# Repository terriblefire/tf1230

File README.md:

# tf1230

TF1230 source files. 

Released in Creative Commons CC-BY-ND license. 

This is a NO DERIVATIVES LICENSE. You cannot modify it and distribute the modified version.

TF1230 is distributed with absolutely no warranty. If you make a mistake you could blow up your A1200. I take no responsibility for this. 

The TF1230 is an 030 accelerator fixed at 50Mhz with 64Mb of SDRAM (128Mb possible), and is intended to work with CF cards or IDE2SD card type devices. The IDE interface does not work with long cables. It is intended to be CHEAP Because thats pretty much all Amiga users care about. You need the ehide.device to use the onboard ide.

There was a design decision to make with the TF ide. Do we make it work as the default ide device and break PCMCIA support, do we add a rom on the card (and more expense) or do we just provide a driver that you can put in a cheap rom and run that way (or just run from disk). I figured the cheapest and least invasive option was the best for a home build solution.

**Before you start building :- You can buy these from Supaduper & AlenPPC (AmiBay) completely built for less than it will cost you to buy the parts and the time it will take you if you bill your time at minimum wage.**

Also do not ask me to reroute the board to a different DRC so you can use your local boardhouse. I dont feel like spending 100 hours of my time to save you $10. The DRC on this board is 7-7-7 and any boardhouse that doesnt totally suck can do this. Also it 4 layer and dont ask if i can be made 2 layer. The answer is no. 

If you need help with this the best place to get it is the exxos forum https://www.exxoshost.co.uk/forum/ 

The SDRAM Controller is derived from my Archie core and the clock controller code is designed to simulate a PLL with adjustable phase. 

This is not an exercise in German over engineering. Its engineered to do an exact task and nothing more. You will need to do the timing fixes or put a clock buffer on the clock line on this board. I didnt do this because i believe that the timing changes are needed on Amigas and not doing them is bad for them long term. Cards that let you get away without doing it are doing you a diservice. It would be like cards letting you go longer without a recap. Its 

That said you are free to sell this on your webshop provided you give credit and do not vastly overprice it. However CE marking is your own issue not mine. AmigaKit may not sell this ever... anyone else can. 

On the other hand if you have an actual firmware bugfix send me a pull request with testing evidence. It will be appreciated greatly. 

For crashes please check that the crash doesnt happen in WinUAE for a A1200 with A1200 IDE and 64MB ZIII Ram before making a bug report. Most of the crashes we have seen over the years are repeatable in that environment.

The purpose of this card is for you to get more enjoyment from your Amiga for very little money. Please do that.

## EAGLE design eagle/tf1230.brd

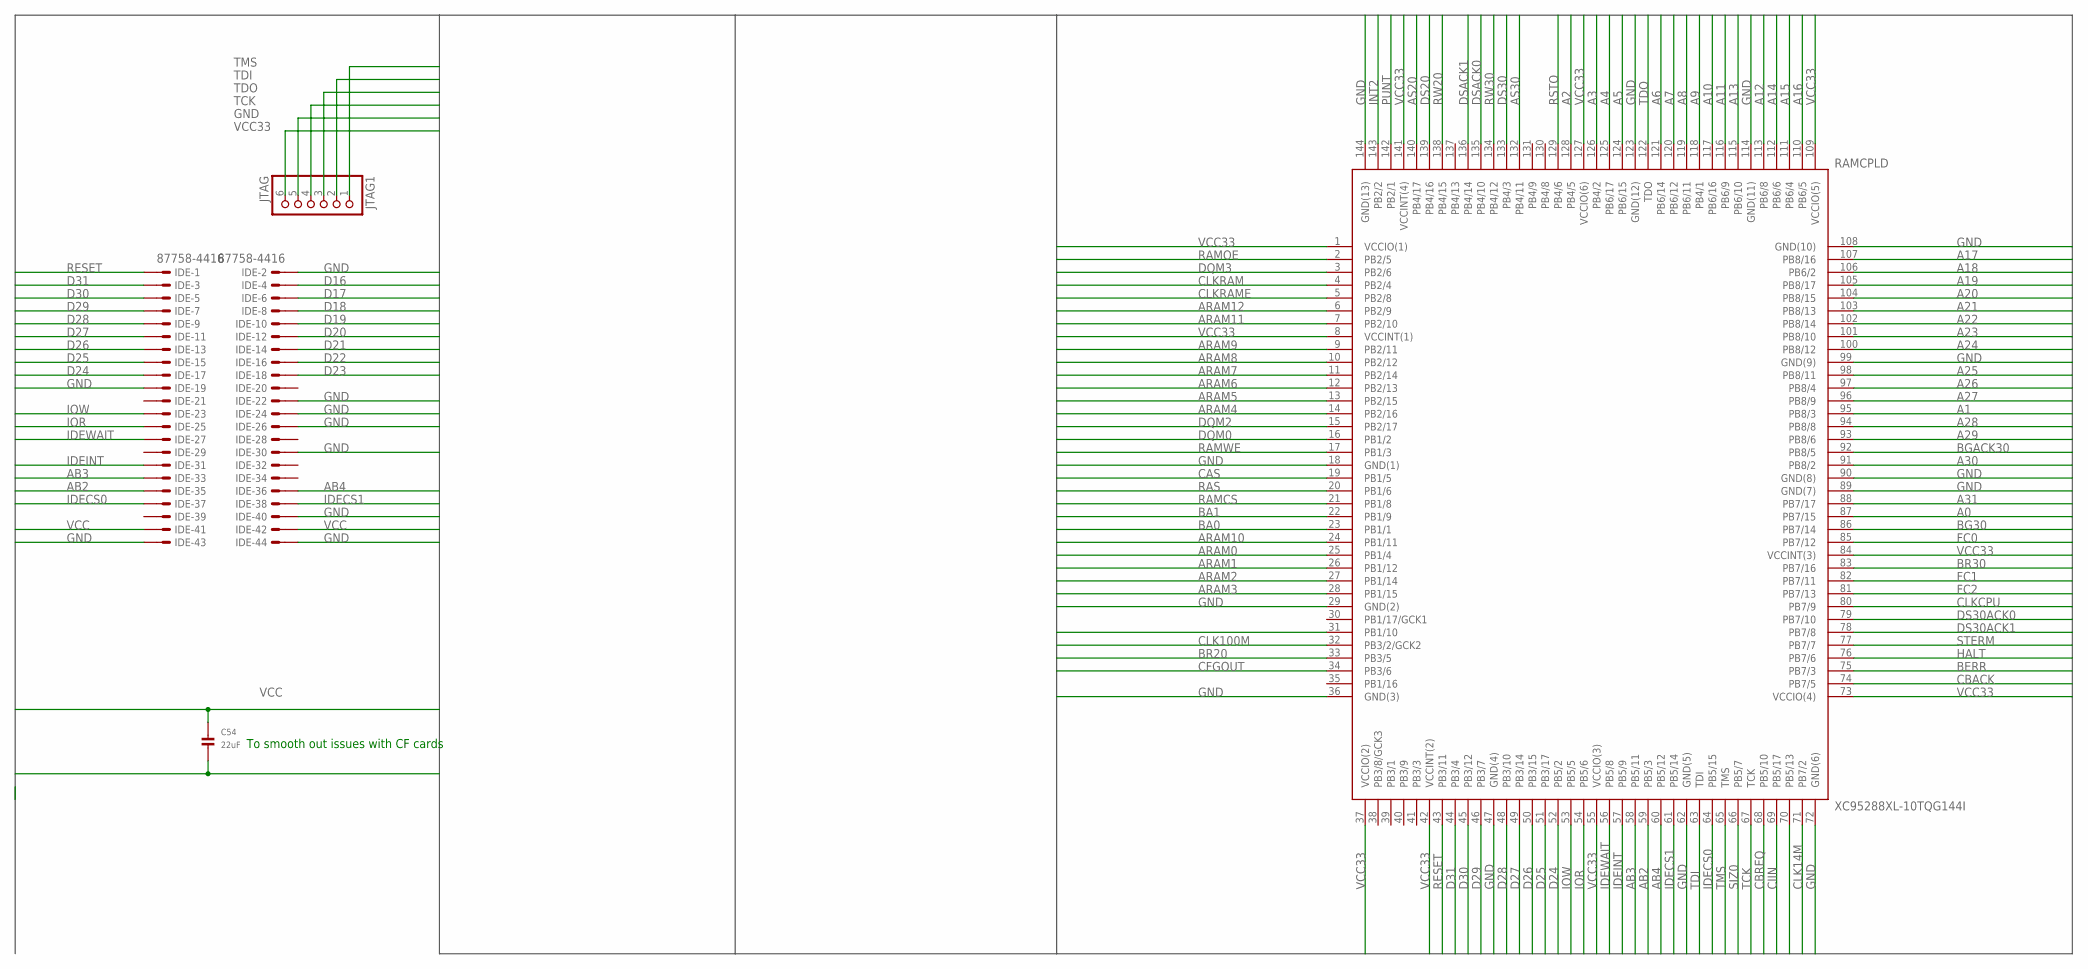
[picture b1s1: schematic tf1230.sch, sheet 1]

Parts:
C54: 22uF; 1206
IDE: 87758-4416
JTAG1: JTAG; 1X06_ROUND
RAMCPLD: XC95288XL-10TQG144I; SAMACSYS_PARTS_QFP50P2200X2200X160-144N

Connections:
A0: RAMCPLD.87 (PB7/15); also elsewhere on the board
A1: RAMCPLD.95 (PB8/3); also elsewhere on the board
A2: RAMCPLD.128 (PB4/5); also elsewhere on the board
A3: RAMCPLD.126 (PB4/2); also elsewhere on the board
A4: RAMCPLD.125 (PB6/17); also elsewhere on the board
A5: RAMCPLD.124 (PB6/15); also elsewhere on the board
A6: RAMCPLD.121 (PB6/14); also elsewhere on the board
A7: RAMCPLD.120 (PB6/12); also elsewhere on the board
A8: RAMCPLD.119 (PB6/11); also elsewhere on the board
A9: RAMCPLD.118 (PB4/1); also elsewhere on the board
A10: RAMCPLD.117 (PB6/16); also elsewhere on the board
A11: RAMCPLD.116 (PB6/9); also elsewhere on the board
A12: RAMCPLD.113 (PB6/8); also elsewhere on the board
A13: RAMCPLD.115 (PB6/10); also elsewhere on the board
A14: RAMCPLD.112 (PB6/6); also elsewhere on the board
A15: RAMCPLD.111 (PB6/4); also elsewhere on the board
A16: RAMCPLD.110 (PB6/5); also elsewhere on the board
A17: RAMCPLD.107 (PB8/16); also elsewhere on the board
A18: RAMCPLD.106 (PB6/2); also elsewhere on the board
A19: RAMCPLD.105 (PB8/17); also elsewhere on the board
A20: RAMCPLD.104 (PB8/15); also elsewhere on the board
A21: RAMCPLD.103 (PB8/13); also elsewhere on the board
A22: RAMCPLD.102 (PB8/14); also elsewhere on the board
A23: RAMCPLD.101 (PB8/10); also elsewhere on the board
A24: RAMCPLD.100 (PB8/12); also elsewhere on the board
A25: RAMCPLD.98 (PB8/11); also elsewhere on the board
A26: RAMCPLD.97 (PB8/4); also elsewhere on the board
A27: RAMCPLD.96 (PB8/9); also elsewhere on the board
A28: RAMCPLD.94 (PB8/8); also elsewhere on the board
A29: RAMCPLD.93 (PB8/6); also elsewhere on the board
A30: RAMCPLD.91 (PB8/2); also elsewhere on the board
A31: RAMCPLD.88 (PB7/17); also elsewhere on the board
AB2: IDE.35, RAMCPLD.59 (PB5/3)
AB3: IDE.33, RAMCPLD.58 (PB5/11)
AB4: IDE.36, RAMCPLD.60 (PB5/12)
ARAM0: RAMCPLD.25 (PB1/4); also elsewhere on the board
ARAM1: RAMCPLD.26 (PB1/12); also elsewhere on the board
ARAM2: RAMCPLD.27 (PB1/14); also elsewhere on the board
ARAM3: RAMCPLD.28 (PB1/15); also elsewhere on the board
ARAM4: RAMCPLD.14 (PB2/16); also elsewhere on the board
ARAM5: RAMCPLD.13 (PB2/15); also elsewhere on the board
ARAM6: RAMCPLD.12 (PB2/13); also elsewhere on the board
ARAM7: RAMCPLD.11 (PB2/14); also elsewhere on the board
ARAM8: RAMCPLD.10 (PB2/12); also elsewhere on the board
ARAM9: RAMCPLD.9 (PB2/11); also elsewhere on the board
ARAM10: RAMCPLD.24 (PB1/11); also elsewhere on the board
ARAM11: RAMCPLD.7 (PB2/10); also elsewhere on the board
ARAM12: RAMCPLD.6 (PB2/9); also elsewhere on the board
AS20: RAMCPLD.140 (PB4/17); also elsewhere on the board
AS30: RAMCPLD.132 (PB4/11); also elsewhere on the board
BA0: RAMCPLD.23 (PB1/1); also elsewhere on the board
BA1: RAMCPLD.22 (PB1/9); also elsewhere on the board
BERR: RAMCPLD.75 (PB7/3); also elsewhere on the board
BG30: RAMCPLD.86 (PB7/14); also elsewhere on the board
BGACK30: RAMCPLD.92 (PB8/5); also elsewhere on the board
BR20: RAMCPLD.33 (PB3/5); also elsewhere on the board
BR30: RAMCPLD.83 (PB7/16); also elsewhere on the board
CAS: RAMCPLD.19 (PB1/5); also elsewhere on the board
CBACK: RAMCPLD.74 (PB7/5); also elsewhere on the board
CBREQ: RAMCPLD.68 (PB5/10); also elsewhere on the board
CFGOUT: RAMCPLD.34 (PB3/6); also elsewhere on the board
CIIN: RAMCPLD.69 (PB5/17); also elsewhere on the board
CLK14M: RAMCPLD.71 (PB7/2); also elsewhere on the board
CLK100M: RAMCPLD.32 (PB3/2/GCK2); also elsewhere on the board
CLKCPU: RAMCPLD.80 (PB7/9); also elsewhere on the board
CLKRAM: RAMCPLD.4 (PB2/4); also elsewhere on the board
CLKRAME: RAMCPLD.5 (PB2/8); also elsewhere on the board
D16: IDE.4; also elsewhere on the board
D17: IDE.6; also elsewhere on the board
D18: IDE.8; also elsewhere on the board
D19: IDE.10; also elsewhere on the board
D20: IDE.12; also elsewhere on the board
D21: IDE.14; also elsewhere on the board
D22: IDE.16; also elsewhere on the board
D23: IDE.18; also elsewhere on the board
D24: IDE.17, RAMCPLD.52 (PB5/2); also elsewhere on the board
D25: IDE.15, RAMCPLD.51 (PB3/17); also elsewhere on the board
D26: IDE.13, RAMCPLD.50 (PB3/15); also elsewhere on the board
D27: IDE.11, RAMCPLD.49 (PB3/14); also elsewhere on the board
D28: IDE.9, RAMCPLD.48 (PB3/10); also elsewhere on the board
D29: IDE.7, RAMCPLD.46 (PB3/7); also elsewhere on the board
D30: IDE.5, RAMCPLD.45 (PB3/12); also elsewhere on the board
D31: IDE.3, RAMCPLD.44 (PB3/4); also elsewhere on the board
DQM0: RAMCPLD.16 (PB1/2); also elsewhere on the board
DQM1: RAMCPLD.31 (PB1/10); also elsewhere on the board
DQM2: RAMCPLD.15 (PB2/17); also elsewhere on the board
DQM3: RAMCPLD.3 (PB2/6); also elsewhere on the board
DS20: RAMCPLD.139 (PB4/16); also elsewhere on the board
DS30: RAMCPLD.133 (PB4/3); also elsewhere on the board
DS30ACK0: RAMCPLD.79 (PB7/10); also elsewhere on the board
DS30ACK1: RAMCPLD.78 (PB7/8); also elsewhere on the board
DSACK0: RAMCPLD.135 (PB4/10); also elsewhere on the board
DSACK1: RAMCPLD.136 (PB4/14); also elsewhere on the board
FC0: RAMCPLD.85 (PB7/12); also elsewhere on the board
FC1: RAMCPLD.82 (PB7/11); also elsewhere on the board
FC2: RAMCPLD.81 (PB7/13); also elsewhere on the board
GND: C54.2, IDE.2, IDE.19, IDE.22, IDE.24, IDE.26, IDE.30, IDE.40, IDE.43, IDE.44, JTAG1.5, RAMCPLD.18 (GND(1)), RAMCPLD.29 (GND(2)), RAMCPLD.36 (GND(3)), RAMCPLD.47 (GND(4)), RAMCPLD.62 (GND(5)), RAMCPLD.72 (GND(6)), RAMCPLD.89 (GND(7)), RAMCPLD.90 (GND(8)), RAMCPLD.99 (GND(9)), RAMCPLD.108 (GND(10)), RAMCPLD.114 (GND(11)), RAMCPLD.123 (GND(12)), RAMCPLD.144 (GND(13)); also elsewhere on the board
HALT: RAMCPLD.76 (PB7/6); also elsewhere on the board
IDECS0: IDE.37, RAMCPLD.64 (PB5/15)
IDECS1: IDE.38, RAMCPLD.61 (PB5/14)
IDEINT: IDE.31, RAMCPLD.57 (PB5/9); also elsewhere on the board
IDEWAIT: IDE.27, RAMCPLD.56 (PB5/8); also elsewhere on the board
INT2: RAMCPLD.143 (PB2/2); also elsewhere on the board
IOR: IDE.25, RAMCPLD.54 (PB5/6)
IOW: IDE.23, RAMCPLD.53 (PB5/5)
PUNT: RAMCPLD.142 (PB2/1); also elsewhere on the board
RAMCS: RAMCPLD.21 (PB1/8); also elsewhere on the board
RAMOE: RAMCPLD.2 (PB2/5); also elsewhere on the board
RAMWE: RAMCPLD.17 (PB1/3); also elsewhere on the board
RAS: RAMCPLD.20 (PB1/6); also elsewhere on the board
RESET: IDE.1, RAMCPLD.43 (PB3/11); also elsewhere on the board
RSTO: RAMCPLD.129 (PB4/6); also elsewhere on the board
RW20: RAMCPLD.138 (PB4/15); also elsewhere on the board
RW30: RAMCPLD.134 (PB4/12); also elsewhere on the board
SIZ0: RAMCPLD.66 (PB5/7); also elsewhere on the board
SIZ1: RAMCPLD.70 (PB5/13); also elsewhere on the board
STERM: RAMCPLD.77 (PB7/7); also elsewhere on the board
TCK: JTAG1.4, RAMCPLD.67 (TCK)
TDI: JTAG1.2, RAMCPLD.63 (TDI)
TDO: JTAG1.3, RAMCPLD.122 (TDO)
TMS: JTAG1.1, RAMCPLD.65 (TMS)
VCC: C54.1, IDE.41, IDE.42; also elsewhere on the board
VCC33: JTAG1.6, RAMCPLD.1 (VCCIO(1)), RAMCPLD.8 (VCCINT(1)), RAMCPLD.37 (VCCIO(2)), RAMCPLD.42 (VCCINT(2)), RAMCPLD.55 (VCCIO(3)), RAMCPLD.73 (VCCIO(4)), RAMCPLD.84 (VCCINT(3)), RAMCPLD.109 (VCCIO(5)), RAMCPLD.127 (VCCIO(6)), RAMCPLD.141 (VCCINT(4)); also elsewhere on the board

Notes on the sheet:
To smooth out issues with CF cards

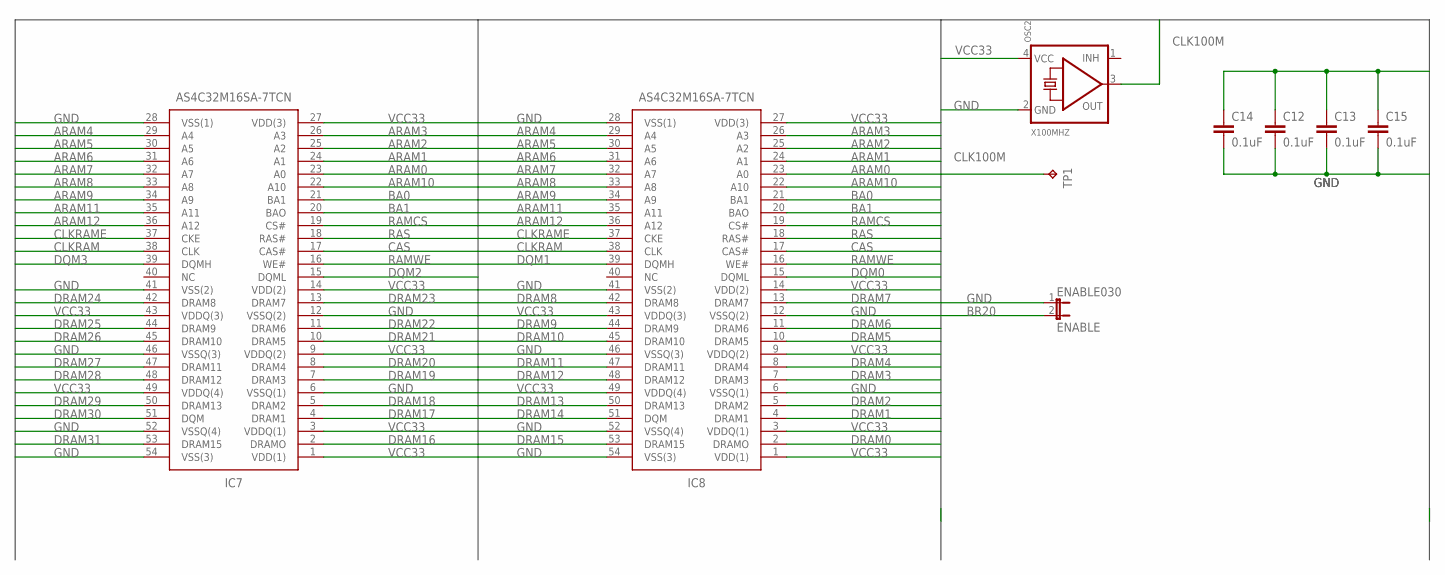
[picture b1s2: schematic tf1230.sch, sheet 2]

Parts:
C12, C13, C14, C15: 0.1uF; 0603-CAP
ENABLE030: ENABLE; 1X02
IC7, IC8: AS4C32M16SA-7TCN; SOP80P1176X120-54N
OSC2: X100MHZ; OSC_7X5MM
TP1: TPB1,27; B1,27

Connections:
ARAM0: IC7.23 (A0), IC8.23 (A0); also elsewhere on the board
ARAM1: IC7.24 (A1), IC8.24 (A1); also elsewhere on the board
ARAM2: IC7.25 (A2), IC8.25 (A2); also elsewhere on the board
ARAM3: IC7.26 (A3), IC8.26 (A3); also elsewhere on the board
ARAM4: IC7.29 (A4), IC8.29 (A4); also elsewhere on the board
ARAM5: IC7.30 (A5), IC8.30 (A5); also elsewhere on the board
ARAM6: IC7.31 (A6), IC8.31 (A6); also elsewhere on the board
ARAM7: IC7.32 (A7), IC8.32 (A7); also elsewhere on the board
ARAM8: IC7.33 (A8), IC8.33 (A8); also elsewhere on the board
ARAM9: IC7.34 (A9), IC8.34 (A9); also elsewhere on the board
ARAM10: IC7.22 (A10), IC8.22 (A10); also elsewhere on the board
ARAM11: IC7.35 (A11), IC8.35 (A11); also elsewhere on the board
ARAM12: IC7.36 (A12), IC8.36 (A12); also elsewhere on the board
BA0: IC7.21 (BA1), IC8.21 (BA1); also elsewhere on the board
BA1: IC7.20 (BAO), IC8.20 (BAO); also elsewhere on the board
BR20: ENABLE030.2; also elsewhere on the board
CAS: IC7.17 (CAS#), IC8.17 (CAS#); also elsewhere on the board
CLK100M: OSC2.3 (OUT), TP1.TP; also elsewhere on the board
CLKRAM: IC7.38 (CLK), IC8.38 (CLK); also elsewhere on the board
CLKRAME: IC7.37 (CKE), IC8.37 (CKE); also elsewhere on the board
DQM0: IC8.15 (DQML); also elsewhere on the board
DQM1: IC8.39 (DQMH); also elsewhere on the board
DQM2: IC7.15 (DQML); also elsewhere on the board
DQM3: IC7.39 (DQMH); also elsewhere on the board
DRAM0: IC8.2 (DRAMO); also elsewhere on the board
DRAM1: IC8.4 (DRAM1); also elsewhere on the board
DRAM2: IC8.5 (DRAM2); also elsewhere on the board
DRAM3: IC8.7 (DRAM3); also elsewhere on the board
DRAM4: IC8.8 (DRAM4); also elsewhere on the board
DRAM5: IC8.10 (DRAM5); also elsewhere on the board
DRAM6: IC8.11 (DRAM6); also elsewhere on the board
DRAM7: IC8.13 (DRAM7); also elsewhere on the board
DRAM8: IC8.42 (DRAM8); also elsewhere on the board
DRAM9: IC8.44 (DRAM9); also elsewhere on the board
DRAM10: IC8.45 (DRAM10); also elsewhere on the board
DRAM11: IC8.47 (DRAM11); also elsewhere on the board
DRAM12: IC8.48 (DRAM12); also elsewhere on the board
DRAM13: IC8.50 (DRAM13); also elsewhere on the board
DRAM14: IC8.51 (DQM); also elsewhere on the board
DRAM15: IC8.53 (DRAM15); also elsewhere on the board
DRAM16: IC7.2 (DRAMO); also elsewhere on the board
DRAM17: IC7.4 (DRAM1); also elsewhere on the board
DRAM18: IC7.5 (DRAM2); also elsewhere on the board
DRAM19: IC7.7 (DRAM3); also elsewhere on the board
DRAM20: IC7.8 (DRAM4); also elsewhere on the board
DRAM21: IC7.10 (DRAM5); also elsewhere on the board
DRAM22: IC7.11 (DRAM6); also elsewhere on the board
DRAM23: IC7.13 (DRAM7); also elsewhere on the board
DRAM24: IC7.42 (DRAM8); also elsewhere on the board
DRAM25: IC7.44 (DRAM9); also elsewhere on the board
DRAM26: IC7.45 (DRAM10); also elsewhere on the board
DRAM27: IC7.47 (DRAM11); also elsewhere on the board
DRAM28: IC7.48 (DRAM12); also elsewhere on the board
DRAM29: IC7.50 (DRAM13); also elsewhere on the board
DRAM30: IC7.51 (DQM); also elsewhere on the board
DRAM31: IC7.53 (DRAM15); also elsewhere on the board
GND: C12.2, C13.2, C14.2, C15.2, ENABLE030.1, IC7.6 (VSSQ(1)), IC7.12 (VSSQ(2)), IC7.28 (VSS(1)), IC7.41 (VSS(2)), IC7.46 (VSSQ(3)), IC7.52 (VSSQ(4)), IC7.54 (VSS(3)), IC8.6 (VSSQ(1)), IC8.12 (VSSQ(2)), IC8.28 (VSS(1)), IC8.41 (VSS(2)), IC8.46 (VSSQ(3)), IC8.52 (VSSQ(4)), IC8.54 (VSS(3)), OSC2.2 (GND); also elsewhere on the board
RAMCS: IC7.19 (CS#), IC8.19 (CS#); also elsewhere on the board
RAMWE: IC7.16 (WE#), IC8.16 (WE#); also elsewhere on the board
RAS: IC7.18 (RAS#), IC8.18 (RAS#); also elsewhere on the board
VCC: C12.1, C13.1, C14.1, C15.1; also elsewhere on the board
VCC33: IC7.1 (VDD(1)), IC7.3 (VDDQ(1)), IC7.9 (VDDQ(2)), IC7.14 (VDD(2)), IC7.27 (VDD(3)), IC7.43 (VDDQ(3)), IC7.49 (VDDQ(4)), IC8.1 (VDD(1)), IC8.3 (VDDQ(1)), IC8.9 (VDDQ(2)), IC8.14 (VDD(2)), IC8.27 (VDD(3)), IC8.43 (VDDQ(3)), IC8.49 (VDDQ(4)), OSC2.4 (VCC); also elsewhere on the board

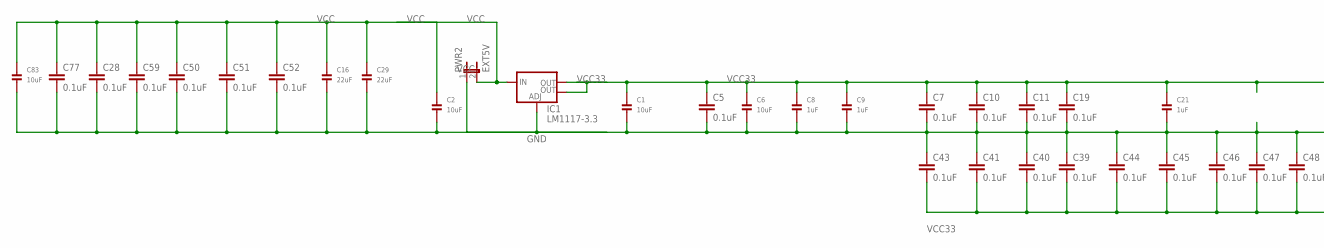
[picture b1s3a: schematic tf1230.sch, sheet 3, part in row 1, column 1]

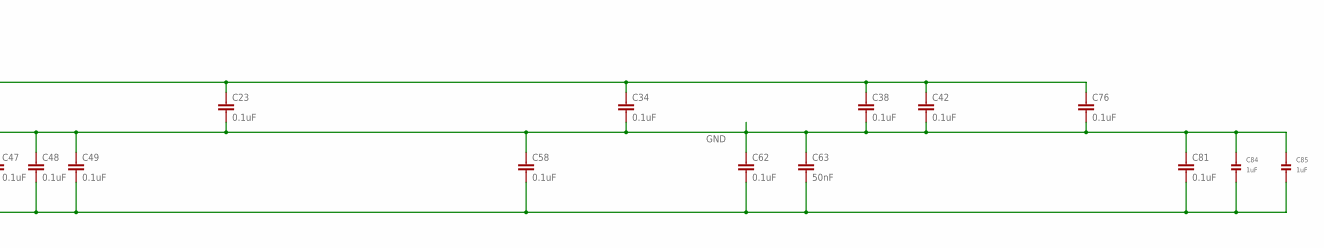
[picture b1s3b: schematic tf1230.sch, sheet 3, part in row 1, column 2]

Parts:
C1, C2, C6, C83: 10uF; 1206
C5, C7, C10, C11, C19, C23, C28, C34, C38, C39, C40, C41, C42, C43, C44, C45, C46, C47, C48, C49, C50, C51, C52, C58, C59, C62, C76, C77, C81: 0.1uF; 0603-CAP
C8, C9, C21, C84, C85: 1uF; 1206
C16, C29: 22uF; 1206
C63: 50nF; 0603-CAP
IC1: LM1117-3.3; SOT223
PWR2: EXT5V; 1X02

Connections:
GND: C1.2, C2.2, C5.2, C6.2, C7.2, C8.2, C9.2, C10.2, C11.2, C16.2, C19.2, C21.2, C23.2, C28.2, C29.2, C34.2, C38.2, C39.1, C40.1, C41.1, C42.2, C43.1, C44.1, C45.1, C46.1, C47.1, C48.1, C49.1, C50.2, C51.2, C52.2, C58.1, C59.2, C62.1, C63.1, C76.2, C77.2, C81.1, C83.2, C84.1, C85.1, IC1.1 (ADJ), PWR2.1; also elsewhere on the board
VCC: C2.1, C16.1, C28.1, C29.1, C50.1, C51.1, C52.1, C59.1, C77.1, C83.1, IC1.3 (IN), PWR2.2; also elsewhere on the board
VCC33: C1.1, C5.1, C6.1, C7.1, C8.1, C9.1, C10.1, C11.1, C19.1, C21.1, C23.1, C34.1, C38.1, C39.2, C40.2, C41.2, C42.1, C43.2, C44.2, C45.2, C46.2, C47.2, C48.2, C49.2, C58.2, C62.2, C63.2, C76.1, C81.2, C84.2, C85.2, IC1.2 (OUT), IC1.4 (OUT); also elsewhere on the board

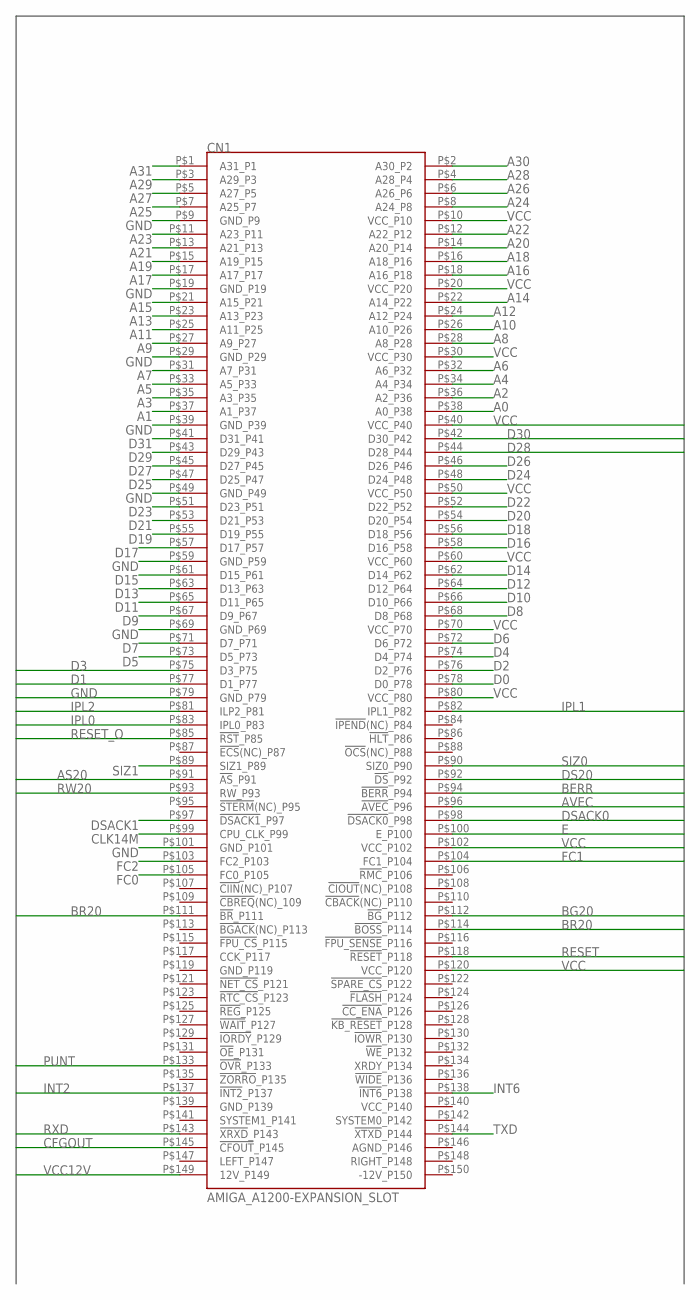
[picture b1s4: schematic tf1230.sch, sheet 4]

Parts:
CN1: AMIGA_A1200-EXPANSION_SLOT; AMIGA_CON_150

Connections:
A0: CN1.P$38 (A0_P38); also elsewhere on the board
A1: CN1.P$37 (A1_P37); also elsewhere on the board
A2: CN1.P$36 (A2_P36); also elsewhere on the board
A3: CN1.P$35 (A3_P35); also elsewhere on the board
A4: CN1.P$34 (A4_P34); also elsewhere on the board
A5: CN1.P$33 (A5_P33); also elsewhere on the board
A6: CN1.P$32 (A6_P32); also elsewhere on the board
A7: CN1.P$31 (A7_P31); also elsewhere on the board
A8: CN1.P$28 (A8_P28); also elsewhere on the board
A9: CN1.P$27 (A9_P27); also elsewhere on the board
A10: CN1.P$26 (A10_P26); also elsewhere on the board
A11: CN1.P$25 (A11_P25); also elsewhere on the board
A12: CN1.P$24 (A12_P24); also elsewhere on the board
A13: CN1.P$23 (A13_P23); also elsewhere on the board
A14: CN1.P$22 (A14_P22); also elsewhere on the board
A15: CN1.P$21 (A15_P21); also elsewhere on the board
A16: CN1.P$18 (A16_P18); also elsewhere on the board
A17: CN1.P$17 (A17_P17); also elsewhere on the board
A18: CN1.P$16 (A18_P16); also elsewhere on the board
A19: CN1.P$15 (A19_P15); also elsewhere on the board
A20: CN1.P$14 (A20_P14); also elsewhere on the board
A21: CN1.P$13 (A21_P13); also elsewhere on the board
A22: CN1.P$12 (A22_P12); also elsewhere on the board
A23: CN1.P$11 (A23_P11); also elsewhere on the board
A24: CN1.P$8 (A24_P8); also elsewhere on the board
A25: CN1.P$7 (A25_P7); also elsewhere on the board
A26: CN1.P$6 (A26_P6); also elsewhere on the board
A27: CN1.P$5 (A27_P5); also elsewhere on the board
A28: CN1.P$4 (A28_P4); also elsewhere on the board
A29: CN1.P$3 (A29_P3); also elsewhere on the board
A30: CN1.P$2 (A30_P2); also elsewhere on the board
A31: CN1.P$1 (A31_P1); also elsewhere on the board
AS20: CN1.P$91 (!AS!_P91); also elsewhere on the board
AVEC: CN1.P$96 (!AVEC!_P96); also elsewhere on the board
BERR: CN1.P$94 (!BERR!_P94); also elsewhere on the board
BG20: CN1.P$112 (!BG!_P112)
BR20: CN1.P$111 (!BR!_P111), CN1.P$114 (!BOSS!_P114); also elsewhere on the board
CFGOUT: CN1.P$145 (!CFOUT!_P145); also elsewhere on the board
CLK14M: CN1.P$99 (CPU_CLK_P99); also elsewhere on the board
D0: CN1.P$78 (D0_P78); also elsewhere on the board
D1: CN1.P$77 (D1_P77); also elsewhere on the board
D2: CN1.P$76 (D2_P76); also elsewhere on the board
D3: CN1.P$75 (D3_P75); also elsewhere on the board
D4: CN1.P$74 (D4_P74); also elsewhere on the board
D5: CN1.P$73 (D5_P73); also elsewhere on the board
D6: CN1.P$72 (D6_P72); also elsewhere on the board
D7: CN1.P$71 (D7_P71); also elsewhere on the board
D8: CN1.P$68 (D8_P68); also elsewhere on the board
D9: CN1.P$67 (D9_P67); also elsewhere on the board
D10: CN1.P$66 (D10_P66); also elsewhere on the board
D11: CN1.P$65 (D11_P65); also elsewhere on the board
D12: CN1.P$64 (D12_P64); also elsewhere on the board
D13: CN1.P$63 (D13_P63); also elsewhere on the board
D14: CN1.P$62 (D14_P62); also elsewhere on the board
D15: CN1.P$61 (D15_P61); also elsewhere on the board
D16: CN1.P$58 (D16_P58); also elsewhere on the board
D17: CN1.P$57 (D17_P57); also elsewhere on the board
D18: CN1.P$56 (D18_P56); also elsewhere on the board
D19: CN1.P$55 (D19_P55); also elsewhere on the board
D20: CN1.P$54 (D20_P54); also elsewhere on the board
D21: CN1.P$53 (D21_P53); also elsewhere on the board
D22: CN1.P$52 (D22_P52); also elsewhere on the board
D23: CN1.P$51 (D23_P51); also elsewhere on the board
D24: CN1.P$48 (D24_P48); also elsewhere on the board
D25: CN1.P$47 (D25_P47); also elsewhere on the board
D26: CN1.P$46 (D26_P46); also elsewhere on the board
D27: CN1.P$45 (D27_P45); also elsewhere on the board
D28: CN1.P$44 (D28_P44); also elsewhere on the board
D29: CN1.P$43 (D29_P43); also elsewhere on the board
D30: CN1.P$42 (D30_P42); also elsewhere on the board
D31: CN1.P$41 (D31_P41); also elsewhere on the board
DS20: CN1.P$92 (!DS!_P92); also elsewhere on the board
DSACK0: CN1.P$98 (!DSACK0!_P98); also elsewhere on the board
DSACK1: CN1.P$97 (!DSACK1!_P97); also elsewhere on the board
E: CN1.P$100 (E_P100)
FC0: CN1.P$105 (FC0_P105); also elsewhere on the board
FC1: CN1.P$104 (FC1_P104); also elsewhere on the board
FC2: CN1.P$103 (FC2_P103); also elsewhere on the board
GND: CN1.P$9 (GND_P9), CN1.P$19 (GND_P19), CN1.P$29 (GND_P29), CN1.P$39 (GND_P39), CN1.P$49 (GND_P49), CN1.P$59 (GND_P59), CN1.P$69 (GND_P69), CN1.P$79 (GND_P79), CN1.P$101 (GND_P101); also elsewhere on the board
INT2: CN1.P$137 (!INT2!_P137); also elsewhere on the board
INT6: CN1.P$138 (!INT6!_P138)
IPL0: CN1.P$83 (IPL0_P83); also elsewhere on the board
IPL1: CN1.P$82 (IPL1_P82); also elsewhere on the board
IPL2: CN1.P$81 (ILP2_P81); also elsewhere on the board
PUNT: CN1.P$133 (!OVR!_P133); also elsewhere on the board
RESET: CN1.P$118 (!RESET!_P118); also elsewhere on the board
RESET_O: CN1.P$85 (!RST!_P85); also elsewhere on the board
RW20: CN1.P$93 (RW_P93); also elsewhere on the board
RXD: CN1.P$143 (!XRXD!_P143)
SIZ0: CN1.P$90 (SIZ0_P90); also elsewhere on the board
SIZ1: CN1.P$89 (SIZ1_P89); also elsewhere on the board
TXD: CN1.P$144 (!XTXD!_P144)
VCC: CN1.P$10 (VCC_P10), CN1.P$20 (VCC_P20), CN1.P$30 (VCC_P30), CN1.P$40 (VCC_P40), CN1.P$50 (VCC_P50), CN1.P$60 (VCC_P60), CN1.P$70 (VCC_P70), CN1.P$80 (VCC_P80), CN1.P$102 (VCC_P102), CN1.P$120 (VCC_P120); also elsewhere on the board
VCC12V: CN1.P$149 (12V_P149)

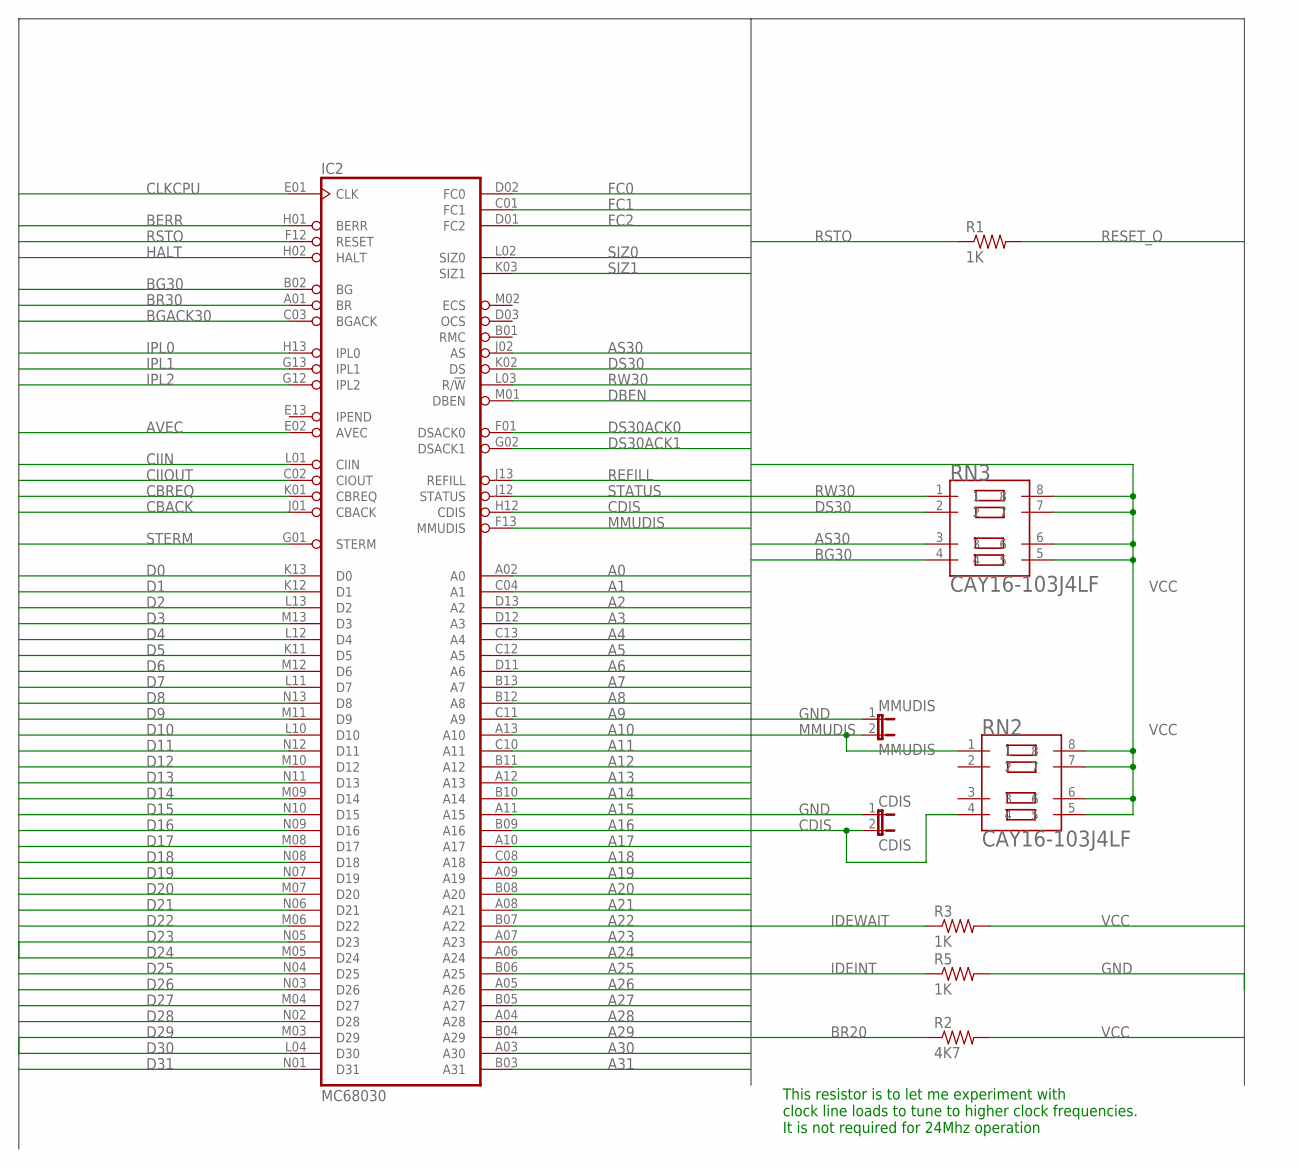
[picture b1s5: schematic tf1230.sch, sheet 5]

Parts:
CDIS: CDIS; 1X02
IC2: MC68030; MPGA128
MMUDIS: MMUDIS; 1X02
R1, R3, R5: 1K; 0603
R2: 4K7; 0603
RN2, RN3: CAY16-103J4LF; RESCAXE80P320X160-8N

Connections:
A0: IC2.A02 (A0); also elsewhere on the board
A1: IC2.C04 (A1); also elsewhere on the board
A2: IC2.D13 (A2); also elsewhere on the board
A3: IC2.D12 (A3); also elsewhere on the board
A4: IC2.C13 (A4); also elsewhere on the board
A5: IC2.C12 (A5); also elsewhere on the board
A6: IC2.D11 (A6); also elsewhere on the board
A7: IC2.B13 (A7); also elsewhere on the board
A8: IC2.B12 (A8); also elsewhere on the board
A9: IC2.C11 (A9); also elsewhere on the board
A10: IC2.A13 (A10); also elsewhere on the board
A11: IC2.C10 (A11); also elsewhere on the board
A12: IC2.B11 (A12); also elsewhere on the board
A13: IC2.A12 (A13); also elsewhere on the board
A14: IC2.B10 (A14); also elsewhere on the board
A15: IC2.A11 (A15); also elsewhere on the board
A16: IC2.B09 (A16); also elsewhere on the board
A17: IC2.A10 (A17); also elsewhere on the board
A18: IC2.C08 (A18); also elsewhere on the board
A19: IC2.A09 (A19); also elsewhere on the board
A20: IC2.B08 (A20); also elsewhere on the board
A21: IC2.A08 (A21); also elsewhere on the board
A22: IC2.B07 (A22); also elsewhere on the board
A23: IC2.A07 (A23); also elsewhere on the board
A24: IC2.A06 (A24); also elsewhere on the board
A25: IC2.B06 (A25); also elsewhere on the board
A26: IC2.A05 (A26); also elsewhere on the board
A27: IC2.B05 (A27); also elsewhere on the board
A28: IC2.A04 (A28); also elsewhere on the board
A29: IC2.B04 (A29); also elsewhere on the board
A30: IC2.A03 (A30); also elsewhere on the board
A31: IC2.B03 (A31); also elsewhere on the board
AS30: IC2.J02 (AS), RN3.3; also elsewhere on the board
AVEC: IC2.E02 (AVEC); also elsewhere on the board
BERR: IC2.H01 (BERR); also elsewhere on the board
BG30: IC2.B02 (BG), RN3.4; also elsewhere on the board
BGACK30: IC2.C03 (BGACK); also elsewhere on the board
BR20: R2.1; also elsewhere on the board
BR30: IC2.A01 (BR); also elsewhere on the board
CBACK: IC2.J01 (CBACK); also elsewhere on the board
CBREQ: IC2.K01 (CBREQ); also elsewhere on the board
CDIS: CDIS.2, IC2.H12 (CDIS), RN2.4
CIIN: IC2.L01 (CIIN); also elsewhere on the board
CIIOUT: IC2.C02 (CIOUT)
CLKCPU: IC2.E01 (CLK); also elsewhere on the board
D0: IC2.K13 (D0); also elsewhere on the board
D1: IC2.K12 (D1); also elsewhere on the board
D2: IC2.L13 (D2); also elsewhere on the board
D3: IC2.M13 (D3); also elsewhere on the board
D4: IC2.L12 (D4); also elsewhere on the board
D5: IC2.K11 (D5); also elsewhere on the board
D6: IC2.M12 (D6); also elsewhere on the board
D7: IC2.L11 (D7); also elsewhere on the board
D8: IC2.N13 (D8); also elsewhere on the board
D9: IC2.M11 (D9); also elsewhere on the board
D10: IC2.L10 (D10); also elsewhere on the board
D11: IC2.N12 (D11); also elsewhere on the board
D12: IC2.M10 (D12); also elsewhere on the board
D13: IC2.N11 (D13); also elsewhere on the board
D14: IC2.M09 (D14); also elsewhere on the board
D15: IC2.N10 (D15); also elsewhere on the board
D16: IC2.N09 (D16); also elsewhere on the board
D17: IC2.M08 (D17); also elsewhere on the board
D18: IC2.N08 (D18); also elsewhere on the board
D19: IC2.N07 (D19); also elsewhere on the board
D20: IC2.M07 (D20); also elsewhere on the board
D21: IC2.N06 (D21); also elsewhere on the board
D22: IC2.M06 (D22); also elsewhere on the board
D23: IC2.N05 (D23); also elsewhere on the board
D24: IC2.M05 (D24); also elsewhere on the board
D25: IC2.N04 (D25); also elsewhere on the board
D26: IC2.N03 (D26); also elsewhere on the board
D27: IC2.M04 (D27); also elsewhere on the board
D28: IC2.N02 (D28); also elsewhere on the board
D29: IC2.M03 (D29); also elsewhere on the board
D30: IC2.L04 (D30); also elsewhere on the board
D31: IC2.N01 (D31); also elsewhere on the board
DBEN: IC2.M01 (DBEN)
DS30: IC2.K02 (DS), RN3.2; also elsewhere on the board
DS30ACK0: IC2.F01 (DSACK0); also elsewhere on the board
DS30ACK1: IC2.G02 (DSACK1); also elsewhere on the board
FC0: IC2.D02 (FC0); also elsewhere on the board
FC1: IC2.C01 (FC1); also elsewhere on the board
FC2: IC2.D01 (FC2); also elsewhere on the board
GND: CDIS.1, IC2.C05 (GND), IC2.C07 (GND), IC2.C09 (GND), IC2.E03 (GND), IC2.E11 (GND), IC2.F03 (GND), IC2.G03 (GND), IC2.G11 (GND), IC2.J03 (GND), IC2.J11 (GND), IC2.L05 (GND), IC2.L07 (GND), IC2.L08 (GND), IC2.L09 (GND), MMUDIS.1, R5.2; also elsewhere on the board
HALT: IC2.H02 (HALT); also elsewhere on the board
IDEINT: R5.1; also elsewhere on the board
IDEWAIT: R3.1; also elsewhere on the board
IPL0: IC2.H13 (IPL0); also elsewhere on the board
IPL1: IC2.G13 (IPL1); also elsewhere on the board
IPL2: IC2.G12 (IPL2); also elsewhere on the board
MMUDIS: IC2.F13 (MMUDIS), MMUDIS.2, RN2.1
REFILL: IC2.J13 (REFILL)
RESET_O: R1.2; also elsewhere on the board
RSTO: IC2.F12 (RESET), R1.1; also elsewhere on the board
RW30: IC2.L03 (R/!W), RN3.1; also elsewhere on the board
SIZ0: IC2.L02 (SIZ0); also elsewhere on the board
SIZ1: IC2.K03 (SIZ1); also elsewhere on the board
STATUS: IC2.J12 (STATUS)
STERM: IC2.G01 (STERM); also elsewhere on the board
VCC: IC2.C06 (VCC), IC2.D04 (VCC), IC2.D10 (VCC), IC2.F02 (VCC), IC2.F11 (VCC), IC2.H03 (VCC), IC2.H11 (VCC), IC2.K04 (VCC), IC2.K10 (VCC), IC2.L06 (VCC), R2.2, R3.2, RN2.5, RN2.6, RN2.7, RN2.8, RN3.5, RN3.6, RN3.7, RN3.8; also elsewhere on the board

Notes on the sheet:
This resistor is to let me experiment with clock line loads to tune to higher clock frequencies. It is not required for 24Mhz operation

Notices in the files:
eagle/tf1230.brd:
(C) 2020 S.J Leary
parts and their libraries:
microbuilder: This work is placed in the public domain, and may be freely used for commercial and non-commercial work with the following conditions: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
SparkFun-Retired: Licensing:Creative Commons ShareAlike 4.0 International - https://creativecommons.org/licenses/by-sa/4.0
